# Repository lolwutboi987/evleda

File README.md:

# EvlEDA

EvlEDA is a local KiCad MCP toolbox and PCB-design skill for agents working in chat. Its workspace tools discover approved stock parts, compile design drafts, create and resume native projects, author schematics and PCB geometry, and collect source-bound checks and previews.

Start with the [toolbox guide](docs/toolbox.md), [client setup](docs/toolbox-client-setup.md), and [current status](docs/current-status-and-roadmap.md). The [PCB skill](skills/evleda-pcb/SKILL.md) supplies the engineering workflow; it does not itself supply CAD access.

The [RP2350 prototype handoff](designs/rp2350-pico/PROTOTYPE-HANDOFF.md) includes
a complete KiCad ZIP. R3 is the owner-selected deliverable; USB inrush remains
explicitly deferred to hardware validation. This is not a manufacturing release.

The [RP2350 R3 candidate](designs/rp2350-pico/native-r3-trace/README.md)
includes the routed 22 x 60 mm four-layer board, schematic, portable library,
previews, pinout and candidate BOM. All 67 nets connect; configured ERC/DRC
and portable schematic parity are clean. R3 removes a redundant 3V3 trace loop
without moving parts or vias. The new topology checker verifies 64 routed nets;
two crystal-net pad shapes remain unsupported. All 62 placement checks pass.
Native save, normal close and fresh read-only reopening are verified.
Engineering acceptance remains incomplete, including USB startup and other
electrical requirements described with the candidate.

- `pnpm mcp:toolbox` serves the verified research corpus without opening CAD.
- `pnpm mcp:toolbox:workspace` uses an explicitly configured host profile and workspace for in-chat draft, create, close and resume operations. See the [disabled configuration example](examples/toolbox-workspace.config.toml) before configuring a host.
- Native authoring is bounded by the selected contract, installed runtime and advertised capabilities. Current source supports the V1 routed family and V2 two- or four-layer plane family; verification status and unsupported cases remain explicit.

The [WSON regulator example](examples/wson-regulator-toolbox-proof/README.md) includes the actual KiCad project, native previews and a compact qualification record. Its public-tool authoring and read-only reopen preserve all six source files; unresolved plane and engineering requirements remain explicit. Native checks produce review evidence, not a manufacture-ready verdict. Physical validation, firmware and manufacturing release are outside this active toolbox milestone.

## Preserved application and Flux UI

The sections below document the earlier application and its profile-bound workflows. Their topology and iteration limits apply to those workflows; they are not a replacement for the current chat toolbox documentation. This infrastructure remains in the repository and is deferred from the active development path.

For the candidate-only local Flux workspace, see [docs/flux-local.md](docs/flux-local.md).

Fresh Flux runs allow 1–24 authoring iterations, with 12 recommended and used
by default. The cap is bound by each new run's approval and does not guarantee
success; consumed runs cannot gain more attempts through a policy update.
Standalone copied-board limits remain 1–5/default 3. See the
[iteration and resource budget policy](docs/flux-local.md#iteration-budgets-and-approval)
for standalone fresh defaults, message/byte limits, and unchanged timeouts.

EvlEDA's broad product goal is a
local-first agentic hardware-development application: turn requirements into
evidence-bound review candidates. It coordinates architecture, component
selection, KiCad sources and checks, firmware contracts, manufacturing
outputs, and bring-up documentation without treating generated output as proof.

The implementation is intentionally narrower than that goal. EvlEDA v0 can
parameterize and replay the reviewed `EVL-RC-G0-REV-A` topology only within its
7-16.8 V, two-channel, at-most-0.5 A RMS-per-channel envelope. It does not yet
generate arbitrary hardware topology. A wider envelope or structural change
requires a separately reviewed immutable profile and native design.

Autonomous work can reach `candidate` only. A model statement, clean native
ERC/DRC, route closure, generated CAM, or successful firmware build does not make
a design safe, fabricated, certified, qualified, flashable, production-ready, or
released. Qualification and manufacturing release are distinct human
attestations bound to exact immutable identities and real evidence.

## Implemented workflow

```text
React operator console ─┐
REST /v1 API ───────────┼── application commands ── nine-stage workflow
EvlEDA MCP server ──────┘             │                    │
                                      │                    ├─ policy gates
                                      │                    ├─ constrained tools
                                      │                    └─ evidence projection
                            durable records + content-addressed artifacts
                                                    │
                              pinned KiCad MCP sidecar / KiCad 10 CLI
```

REST and MCP expose the same 14 public workflow operations, including
`inspect_engineering_practices`. Human-only authority remains unavailable to the
agent-facing MCP process. KiCad remains authoritative for native project
semantics, ERC/DRC, rendering, and exports; EvlEDA owns orchestration, typed
transformations, traceability, evidence freshness, and lifecycle policy.

The repository also contains isolated Phase-A agent scaffolding and architecture
IR: role contracts, production-host prerequisites, an authenticated provider
boundary, durable frozen replay receipts, mandatory deterministic validators,
and a system-architecture IR/compiler. That subsystem is not wired into the
application factory/service, REST, MCP, or React UI, and production composition
has no default live provider. It is implemented and tested infrastructure, not
an active agent-driven design path.

## Honest reference-design status

The canonical six-layer Rev-A source opens cleanly and has source-bound native
results with zero ERC, DRC, schematic-parity, and route-closure findings. Native
cleanliness and EvlEDA's route-practice policy are separate checks, however.
Rev-A is deliberately retained as an expected-negative BLOCKED_DIAGNOSTIC proof fixture
for the hard `ROUTE_STYLE` and `BACKTRACK` rules. Its plan records
`expected_negative`; until bound analyzer evidence proves compliant regenerated
geometry, engineering-practice inspection must report `BLOCKED_DIAGNOSTIC`, not
`PROVISIONAL_POC`, manufacture-ready, or release status.

The normal production workflow is independently blocked earlier at component
selection because the captured buck source is unavailable and all eight pin/pad
reviews remain pending. A clean native board does not waive either boundary.
See [the current handoff](HANDOFF.md), the
[reference-design details](reference-designs/robotics-controller-v0/README.md),
and the [PCB engineering-practice contract](docs/pcb-engineering-practices.md).

## Reproducibility and durable-state boundaries

Current exports use `evleda.bundle-manifest.v3`,
`evleda.bundle-export-replay.v2`, and the `deterministic-zip-v3` tool profile.
The manifest, result, and every bundle-generated artifact bind the canonical
`evleda.live-regeneration-policy.v1` identity as an exact input. Live model or
research regeneration is labeled traceable and non-reproducible.

Original unlabeled `evleda.bundle-manifest.v2` manifests and their
`evleda.bundle-export-replay.v1` envelopes remain exact legacy data: they keep
the `deterministic-zip-v2` two-input contract and are never relabeled or given a
synthesized policy. The standalone verifier rejects them by default; explicit
`--allow-legacy-v2` verification recomputes provenance roots but returns the
downgraded `provenance_roots_without_live_policy` assurance. Legacy
`evleda.bundle-manifest.v1` remains a separate explicit byte-integrity-only mode.

Acceptance row W-03 is software-complete: fault injection covers every content
commit boundary and proves partial stage artifacts/evidence never become current.
One P2 lock-hardening `it.todo` test remains for recycled live-PID and
process-incarnation handling; it does not reopen the atomic-publication result.
W-08 is unverified: native KiCad and firmware report artifacts embed invocation
details and identities, but no production application writer populates the
state schema's reserved `ToolInvocationRecord` map. Embedded report evidence is
not a durable first-class invocation ledger.

## Physical and firmware boundaries

The software implements strict `evleda.physical-acceptance.v2`,
`evleda.physical-measurements.v2`, and `evleda.human-physical-evidence.v3`
contracts and exercises their qualification/release gates with test fixtures.
The canonical Rev-A repository has no real built-board acceptance record,
hardware qualification, or manufacturing release. Software fixtures cannot
supply those facts.

The real STM32G0 cross-build snapshots the pinned Arm GNU toolchain and CMSIS
support closure, executes from a verified private workspace with bounded inputs,
and emits identity-bound ELF/BIN/map outputs. Those outputs remain
`compiled-non-flashable-candidate`, with `flashable: false` and no release
authority.

## Development

Requires Node.js 24.19 or newer, pnpm, and KiCad 10.x for native integration.
The optional real KiCad-MCP smoke setup is documented in
[the sidecar verification guide](docs/kicad-mcp-sidecar.md); the identity-bound
STM32G0 cross-build is documented in
[the firmware toolchain guide](docs/firmware-toolchain.md). The 1,773-rule,
17-dossier engineering corpus is a manifest-bound application resource; its
module-relative loading, identity, packaging, and update procedure are in the
[deep-rule resource guide](docs/deep-rule-resources.md).

```powershell
pnpm install --frozen-lockfile
pnpm verify
pnpm dev
```

Runtime state defaults to a local application-data directory and should not live
in the synced source tree. See [the product contract](docs/product-contract.md)
for normative safety and evidence boundaries.

## Verified matrix (2026-09-05)

The latest local verification used Node 24.19.0 and the explicit pinned tool
paths described in `HANDOFF.md`. Targeted rows overlap and must not be added
together.

- Full `node scripts/check.mjs`: 65/65 test files, 929 passed, 1 skip
  (intentional), 1 todo, and 0 failures.
- UI TypeScript: passed; UI Vitest: 10/10 files and 33/33 tests passed.
- Installed-Chrome Playwright: 5/5 passed.
- Real KiCad/reference suites: 4/4 files and 76/76 tests passed.
- Firmware validation: 32 passed and 1 intentional host-compiler skip because
  `EVLEDA_FIRMWARE_CC` was unset; the real Arm cross-build ran and passed.
- Audited `kicad-mcp`: 5/5 passed.
- Evidence and bundle suites: 3/3 files and 43/43 tests passed; standalone
  bundle adversarial verification: 35/35 passed.
- Production build: passed, 92 modules transformed.

These results do not substitute for GitHub CI, fabrication, bench evidence,
qualification, safety review, or release.

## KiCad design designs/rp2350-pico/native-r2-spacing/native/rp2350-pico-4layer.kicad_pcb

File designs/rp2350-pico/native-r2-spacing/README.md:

# RP2350 R2: corrected crystal-block spacing

This **22 x 60 mm, four-layer review candidate** has 1,098 tracks, 118 vias,
62 electrical components and four mounting bores. All 67 functional nets connect.
Configured native ERC/DRC and portable schematic parity are clean. Native save,
normal close and fresh read-only reopening are verified.

Open [the KiCad project](native/rp2350-pico-4layer.kicad_pro) with KiCad 10.0.3,
its stock libraries and the included native/library directory. The package includes
[top](previews/top.png), [assembly](previews/assembly.png), [schematic](previews/schematic.svg),
[pinout](pinout.md), [candidate BOM](bom-candidates.csv) and [BOM notes](bom-notes.md).
R2 names this delivery package; the retained board silkscreen still reads R1.

## Placement correction

The new reusable checker found a 0.02 mm C12–R7 courtyard gap against the
unchanged 0.10 mm requirement. R7 moves 0.10 mm left and the nearby GND via
moves 0.15 mm down to an existing diagonal endpoint. The redundant 0.15 mm
ground stub is removed. The resulting courtyard gap is **0.12 mm**.
All signal tracks, component rotations, via dimensions and clearance requirements
are preserved. Only R7's placement-region minimum X extends from 9.35 to 9.25 mm.
The [revision record](spacing-revision.json) and original failed baseline are retained.

All **62 placement rows** now pass against actual saved geometry and approved
courtyard sources. This checks the declared region, side, rotation, board-edge
bounds and pair spacing; physical housings, fasteners and assembly tolerances
remain separate. The original R1 remains available as historical evidence.

## Routing and checks

Both full-height GPIO service strips are clear of unrelated copper; 42 exact
own-pad inward leads remain. Header pitch/row spacing stay 2.54/17.78 mm.
The current source audit measures **886 straight/45-degree turns
with zero violations**, retaining 6 generic junction notices
and their pad/via attribution. All 19 declared geometric reference rows and
nominal drilled-copper paths from all 64 physical GND pads to the primary plane
pass. Existing debug-terminal launch conditions and margins remain unchanged.

The original [host60 native assessment](../../../proofs/placement-spacing-20260921/public-report.json)
records **225 pass, 349 unknown, 0 fail; accepted=false**. The newer [host62 assessment](../../../proofs/artifact-checks-20260921/fresh-fill-report.json) on these unchanged native files records **495 pass, 79 unknown, 0 fail; accepted=false** after integrating 270 source/native artifact requirements. Unknowns include
unfinished assessment integration plus electrical and construction requirements;
they are not a count of observed defects. USB attach/startup/inrush, current,
voltage drop, physical copper/thermal widths and interface performance remain
open. The board is not yet an electrically accepted or manufacturing-ready design.

Read-only reopening retains placement results and all 67 connected nets without
recreating the earlier session's fresh-fill authority. Its plane/reference rows
remain unknown as returned. The four portable design files are byte-exact;
only the two library-table URI prefixes change for portability.

The native visual heuristic still reports WARN. Its four reference-overlap
warnings use hidden F.Fab fields; its body/off-board estimates center dimensions
on footprint origins. The [source and preview review](verification/visual-review.json)
retains all 13 findings and the actual header courtyards. Both current previews
were visually inspected. This is not a machine-certified visual or assembly pass.

ERC ignores single_global_label, four_way_junction, simulation_model_issue and
footprint_filter. DRC ignores missing_courtyard, track_not_centered_on_via,
tuning_profile_track_geometries, footprint_filters_mismatch and footprint_type_mismatch.
Complete native reports retain checker settings and exclusions.

## Managed continuation

Continue with project **0474c726-1b0c-492b-b376-9c6a06ee9d72** in the existing qualified workspace.
Both edit and fresh read-only sessions closed normally. Parent **f464e518-2b03-453a-9f9c-a31f7d044d4a**
and the older protected allocation remain preserved. No historical lease or
unsafe marker was removed. Host60 is stored on D:, which must stay mounted.
Firmware, physical testing, board ordering and manufacturing release are outside
this delivered scope.

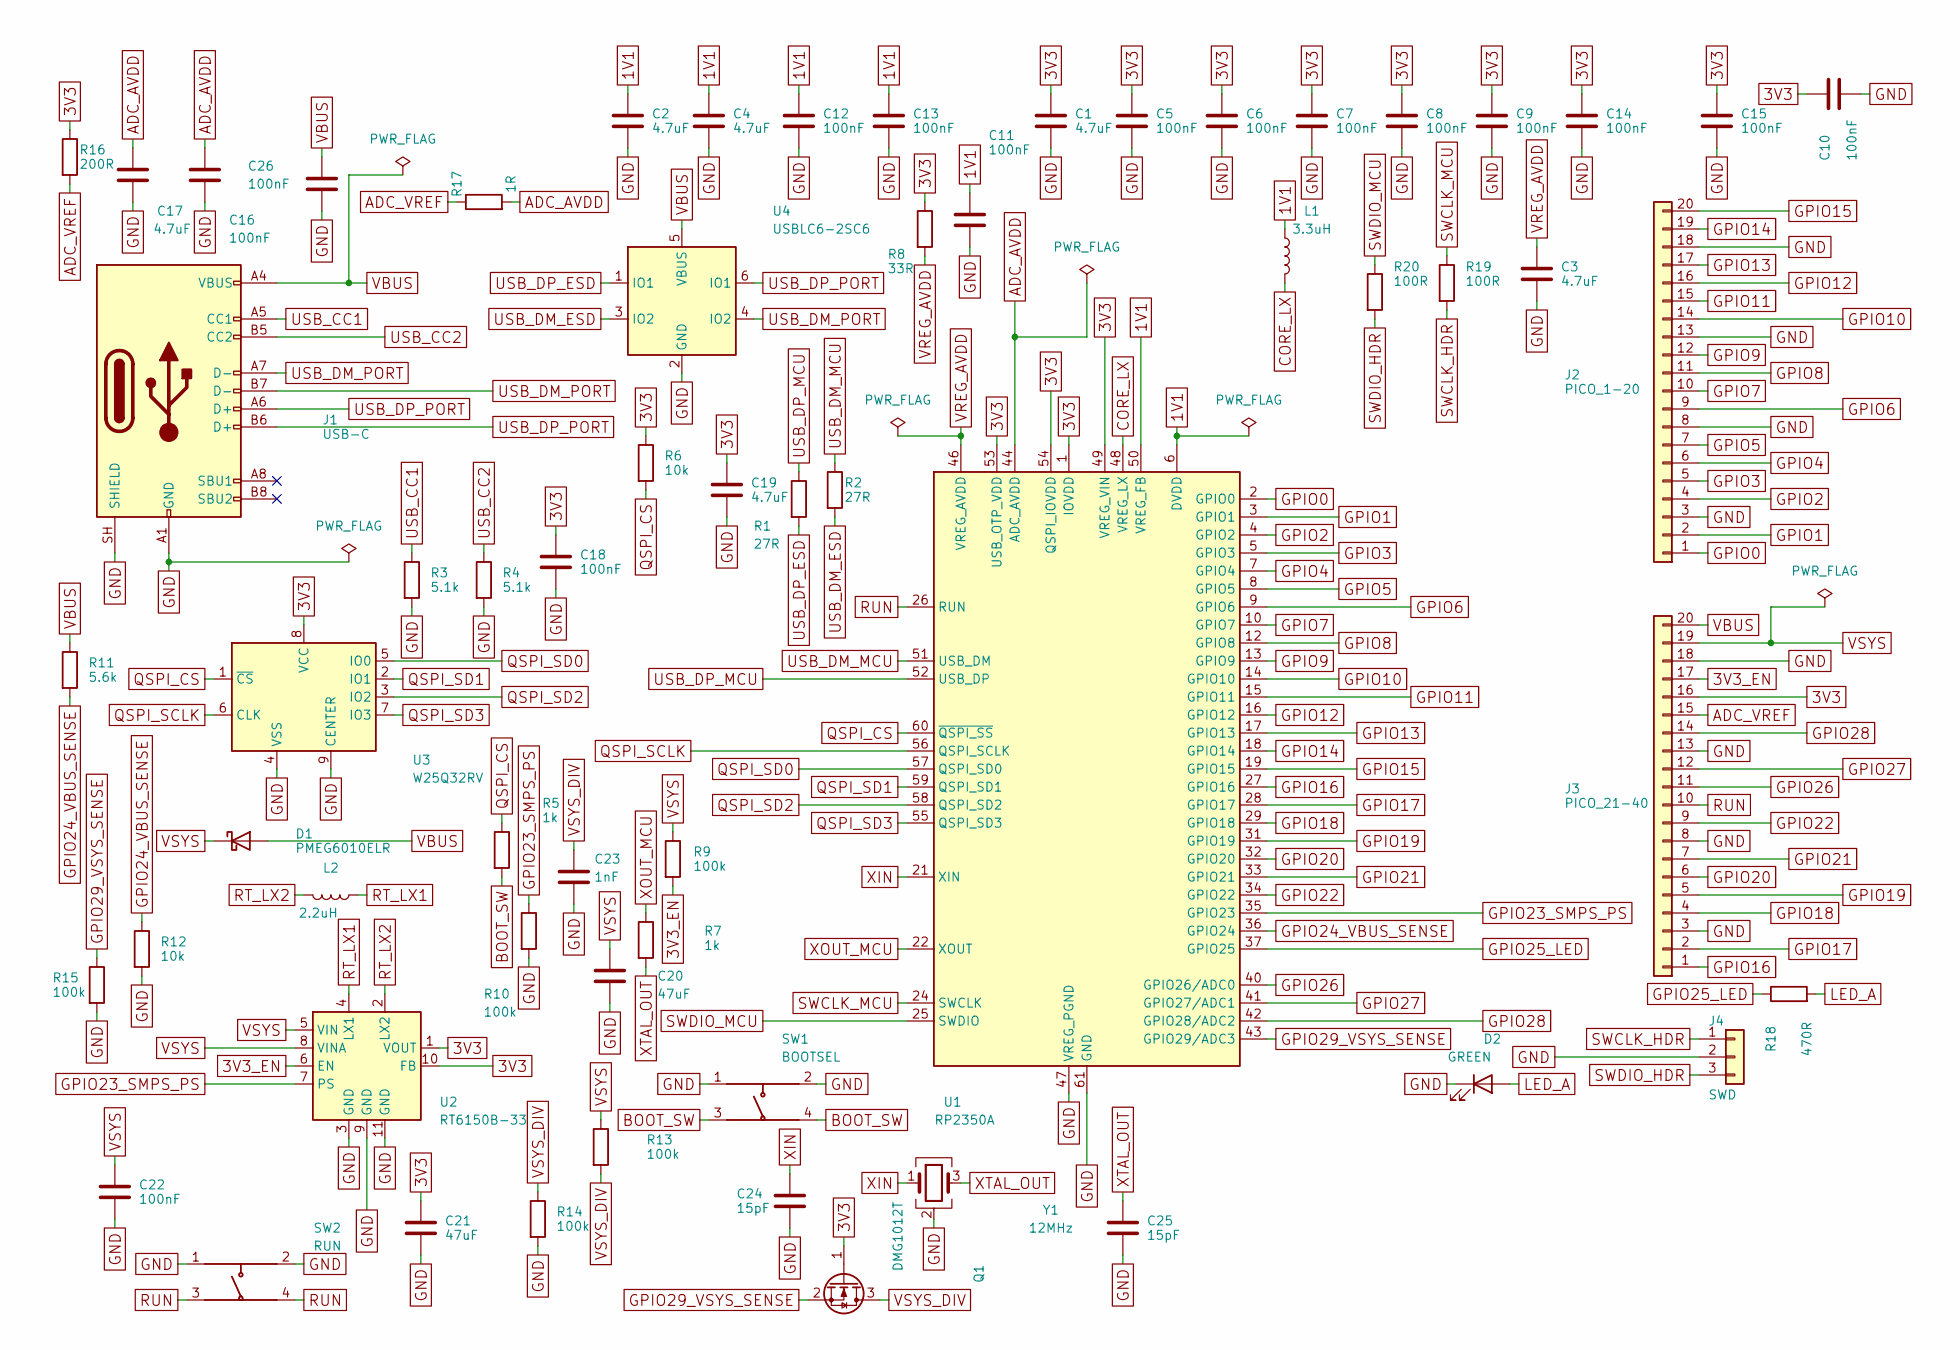
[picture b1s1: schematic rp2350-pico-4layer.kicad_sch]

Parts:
C1, C2, C3, C4, C17, C19: 4.7uF; C_0402_1005Metric
C5, C6, C7, C8, C9, C10, C11, C12, C13, C14, C15, C16, C18, C22, C26: 100nF; C_0402_1005Metric
C20, C21: 47uF; C3225X5R1A476M250AC_TDK_PA2.2_PB1.1_PC2.2
C23: 1nF; C_0402_1005Metric
C24, C25: 15pF; C_0402_1005Metric
D1: PMEG6010ELR; Nexperia_CFP3_SOD-123W
D2: GREEN; LED_0603_1608Metric
J1: USB-C; USB_C_Receptacle_GCT_USB4105-xx-A_16P_TopMnt_Horizontal
J2: PICO_1-20; Pico_BarePTH_1x20_P2.54mm_D1.0mm_Pad1.7mm
J3: PICO_21-40; Pico_BarePTH_1x20_P2.54mm_D1.0mm_Pad1.7mm
J4: SWD; PinHeader_1x03_P2.54mm_Vertical
L1: 3.3uH; AOTA-B201610S3R3-101-T_RaspberryPi_Minimal
L2: 2.2uH; L_Coilcraft_XxL4020
Q1: DMG1012T; SOT-523
R1, R2: 27R; R_0402_1005Metric
R3, R4: 5.1k; R_0402_1005Metric
R5, R7: 1k; R_0402_1005Metric
R6, R12: 10k; R_0402_1005Metric
R8: 33R; R_0402_1005Metric
R9, R10, R13, R14, R15: 100k; R_0402_1005Metric
R11: 5.6k; R_0402_1005Metric
R16: 200R; R_0402_1005Metric
R17: 1R; R_0402_1005Metric
R18: 470R; R_0402_1005Metric
R19, R20: 100R; R_0402_1005Metric
SW1: BOOTSEL; Wuerth_434133025816_4Terminal
SW2: RUN; Wuerth_434133025816_4Terminal
U1: RP2350A; QFN-60-1EP_7x7mm_P0.4mm_EP3.4x3.4mm
U2: RT6150B-33; RT6150B_WDFN-10-1EP_2.5x2.5mm_P0.5mm
U3: W25Q32RV; W25Q32RVXH_XSON-8-1EP_3x2mm_P0.5mm_EP0.2x1.6mm
U4: USBLC6-2SC6; SOT-23-6
Y1: 12MHz; Crystal_SMD_3225-4Pin_3.2x2.5mm

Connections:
1V1: C2.1, C4.1, C11.1, C12.1, C13.1, L1.1, U1.6 (DVDD), U1.23 (DVDD), U1.39 (DVDD), U1.50 (VREG_FB)
3V3: C1.1, C5.1, C6.1, C7.1, C8.1, C9.1, C10.1, C14.1, C15.1, C18.1, C19.1, C21.1, J3.16, Q1.1 (G), R6.1, R8.1, R16.1, U1.1 (IOVDD), U1.11 (IOVDD), U1.20 (IOVDD), U1.30 (IOVDD), U1.38 (IOVDD), U1.45 (IOVDD), U1.49 (VREG_VIN), U1.53 (USB_OTP_VDD), U1.54 (QSPI_IOVDD), U2.1 (VOUT), U2.10 (FB), U3.8 (VCC)
3V3_EN: J3.17, R9.2, U2.6 (EN)
ADC_AVDD: C16.1, C17.1, R17.2, U1.44 (ADC_AVDD)
ADC_VREF: J3.15, R16.2, R17.1
BOOT_SW: R5.2, SW1.3 (B), SW1.4 (B)
CORE_LX: L1.2, U1.48 (VREG_LX)
GND: C1.2, C2.2, C3.2, C4.2, C5.2, C6.2, C7.2, C8.2, C9.2, C10.2, C11.2, C12.2, C13.2, C14.2, C15.2, C16.2, C17.2, C18.2, C19.2, C20.2, C21.2, C22.2, C23.2, C24.2, C25.2, C26.2, D2.1 (K), J1.A1 (GND), J1.A12 (GND), J1.B1 (GND), J1.B12 (GND), J1.SH (SHIELD), J2.3, J2.8, J2.13, J2.18, J3.3, J3.8, J3.13, J3.18, J4.2, R3.2, R4.2, R10.2, R12.2, R14.2, R15.2, SW1.1 (A), SW1.2 (A), SW2.1 (A), SW2.2 (A), U1.47 (VREG_PGND), U1.61 (GND), U2.3 (GND), U2.9 (GND), U2.11 (GND), U3.4 (VSS), U3.9 (CENTER), U4.2 (GND), Y1.2 (G), Y1.4 (G)
GPIO0: J2.1, U1.2 (GPIO0)
GPIO1: J2.2, U1.3 (GPIO1)
GPIO2: J2.4, U1.4 (GPIO2)
GPIO3: J2.5, U1.5 (GPIO3)
GPIO4: J2.6, U1.7 (GPIO4)
GPIO5: J2.7, U1.8 (GPIO5)
GPIO6: J2.9, U1.9 (GPIO6)
GPIO7: J2.10, U1.10 (GPIO7)
GPIO8: J2.11, U1.12 (GPIO8)
GPIO9: J2.12, U1.13 (GPIO9)
GPIO10: J2.14, U1.14 (GPIO10)
GPIO11: J2.15, U1.15 (GPIO11)
GPIO12: J2.16, U1.16 (GPIO12)
GPIO13: J2.17, U1.17 (GPIO13)
GPIO14: J2.19, U1.18 (GPIO14)
GPIO15: J2.20, U1.19 (GPIO15)
GPIO16: J3.1, U1.27 (GPIO16)
GPIO17: J3.2, U1.28 (GPIO17)
GPIO18: J3.4, U1.29 (GPIO18)
GPIO19: J3.5, U1.31 (GPIO19)
GPIO20: J3.6, U1.32 (GPIO20)
GPIO21: J3.7, U1.33 (GPIO21)
GPIO22: J3.9, U1.34 (GPIO22)
GPIO23_SMPS_PS: R10.1, U1.35 (GPIO23), U2.7 (PS)
GPIO24_VBUS_SENSE: R11.2, R12.1, U1.36 (GPIO24)
GPIO25_LED: R18.1, U1.37 (GPIO25)
GPIO26: J3.11, U1.40 (GPIO26/ADC0)
GPIO27: J3.12, U1.41 (GPIO27/ADC1)
GPIO28: J3.14, U1.42 (GPIO28/ADC2)
GPIO29_VSYS_SENSE: Q1.2 (S), R15.1, U1.43 (GPIO29/ADC3)
LED_A: D2.2 (A), R18.2
QSPI_CS: R5.1, R6.2, U1.60 (~QSPI_SS), U3.1 (~CS)
QSPI_SCLK: U1.56 (QSPI_SCLK), U3.6 (CLK)
QSPI_SD0: U1.57 (QSPI_SD0), U3.5 (IO0)
QSPI_SD1: U1.59 (QSPI_SD1), U3.2 (IO1)
QSPI_SD2: U1.58 (QSPI_SD2), U3.3 (IO2)
QSPI_SD3: U1.55 (QSPI_SD3), U3.7 (IO3)
RT_LX1: L2.1, U2.4 (LX1)
RT_LX2: L2.2, U2.2 (LX2)
RUN: J3.10, SW2.3 (B), SW2.4 (B), U1.26 (RUN)
SWCLK_HDR: J4.1, R19.2
SWCLK_MCU: R19.1, U1.24 (SWCLK)
SWDIO_HDR: J4.3, R20.2
SWDIO_MCU: R20.1, U1.25 (SWDIO)
USB_CC1: J1.A5 (CC1), R3.1
USB_CC2: J1.B5 (CC2), R4.1
USB_DM_ESD: R2.2, U4.3 (IO2)
USB_DM_MCU: R2.1, U1.51 (USB_DM)
USB_DM_PORT: J1.A7 (D-), J1.B7 (D-), U4.4 (IO2)
USB_DP_ESD: R1.2, U4.1 (IO1)
USB_DP_MCU: R1.1, U1.52 (USB_DP)
USB_DP_PORT: J1.A6 (D+), J1.B6 (D+), U4.6 (IO1)
VBUS: C26.1, D1.2 (A), J1.A4 (VBUS), J1.A9 (VBUS), J1.B4 (VBUS), J1.B9 (VBUS), J3.20, R11.1, U4.5 (VBUS)
VREG_AVDD: C3.1, R8.2, U1.46 (VREG_AVDD)
VSYS: C20.1, C22.1, D1.1 (K), J3.19, R9.1, R13.1, U2.5 (VIN), U2.8 (VINA)
VSYS_DIV: C23.1, Q1.3 (D), R13.2, R14.1
XIN: C24.1, U1.21 (XIN), Y1.1
XOUT_MCU: R7.1, U1.22 (XOUT)
XTAL_OUT: C25.1, R7.2, Y1.3

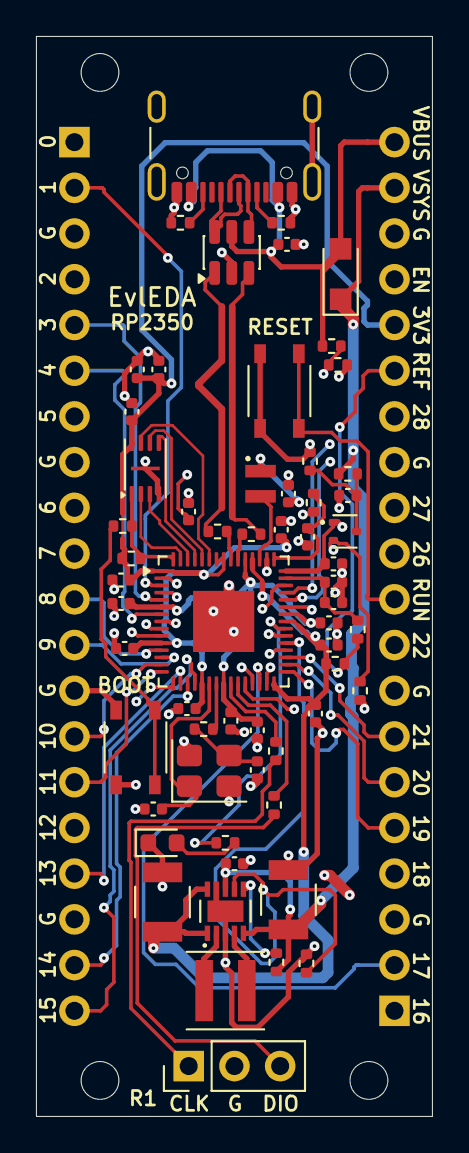
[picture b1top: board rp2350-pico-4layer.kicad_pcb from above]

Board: 4 copper layers, 22.0 x 60.0 mm, 66 parts (0 on the bottom side), 67 nets.

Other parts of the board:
H1, H2, H3, H4: 2.1 mm bare NPTH mounting bore; MountingHole_D2.1_Pico

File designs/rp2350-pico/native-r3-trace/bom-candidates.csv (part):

"reference","quantity","value","mpn","footprint","selectionBasis","sourceIds","notes"
"C1","1","4.7uF","GRM155R60J475ME47D","Capacitor_SMD:C_0402_1005Metric","component-selection.json","K;M47;D;P","Candidate part; retain source conditions and derating"
"C2","1","4.7uF","GRM155R60J475ME47D","Capacitor_SMD:C_0402_1005Metric","component-selection.json","K;M47;D;P","Candidate part; retain source conditions and derating"
"C3","1","4.7uF","GRM155R60J475ME47D","Capacitor_SMD:C_0402_1005Metric","component-selection.json","K;M47;D;P","Candidate part; retain source conditions and derating"
"C4","1","4.7uF","GRM155R60J475ME47D","Capacitor_SMD:C_0402_1005Metric","component-selection.json","K;M47;D;P","Candidate part; retain source conditions and derating"
"C5","1","100nF","GRM155R71E104KE14D","Capacitor_SMD:C_0402_1005Metric","component-selection.json","K;M100","Candidate part; retain source conditions and derating"
"C6","1","100nF","GRM155R71E104KE14D","Capacitor_SMD:C_0402_1005Metric","component-selection.json","K;M100","Candidate part; retain source conditions and derating"
"C7","1","100nF","GRM155R71E104KE14D","Capacitor_SMD:C_0402_1005Metric","component-selection.json","K;M100","Candidate part; retain source conditions and derating"
"C8","1","100nF","GRM155R71E104KE14D","Capacitor_SMD:C_0402_1005Metric","component-selection.json","K;M100","Candidate part; retain source conditions and derating"
"C9","1","100nF","GRM155R71E104KE14D","Capacitor_SMD:C_0402_1005Metric","component-selection.json","K;M100","Candidate part; retain source conditions and derating"
"C10","1","100nF","GRM155R71E104KE14D","Capacitor_SMD:C_0402_1005Metric","component-selection.json","K;M100","Candidate part; retain source conditions and derating"
"C11","1","100nF","GRM155R71E104KE14D","Capacitor_SMD:C_0402_1005Metric","component-selection.json","K;M100","Candidate part; retain source conditions and derating"
"C12","1","100nF","GRM155R71E104KE14D","Capacitor_SMD:C_0402_1005Metric","component-selection.json","K;M100","Candidate part; retain source conditions and derating"
"C13","1","100nF","GRM155R71E104KE14D","Capacitor_SMD:C_0402_1005Metric","component-selection.json","K;M100","Candidate part; retain source conditions and derating"
"C14","1","100nF","GRM155R71E104KE14D","Capacitor_SMD:C_0402_1005Metric","component-selection.json","K;M100","Candidate part; retain source conditions and derating"
"C15","1","100nF","GRM155R71E104KE14D","Capacitor_SMD:C_0402_1005Metric","component-selection.json","K;M100","Candidate part; retain source conditions and derating"
"C16","1","100nF","GRM155R71E104KE14D","Capacitor_SMD:C_0402_1005Metric","component-selection.json","K;M100","Candidate part; retain source conditions and derating"
"C17","1","4.7uF","GRM155R60J475ME47D","Capacitor_SMD:C_0402_1005Metric","component-selection.json","K;M47;D;P","Candidate part; retain source conditions and derating"
"C18","1","100nF","GRM155R71E104KE14D","Capacitor_SMD:C_0402_1005Metric","component-selection.json","K;M100","Candidate part; retain source conditions and derating"
"C19","1","4.7uF","GRM155R60J475ME47D","Capacitor_SMD:C_0402_1005Metric","component-selection.json","K;M47;D;P","Candidate part; retain source conditions and derating"
"C20","1","47uF","C3225X5R1A476M250AC","EvlEDA_Pico2350:C3225X5R1A476M250AC_TDK_PA2.2_PB1.1_PC2.2","component-selection.json","BULK;BULK_CURVE;R;P","Native custom land differs from the earlier stock candidate; see bundled library provenance"
"C21","1","47uF","C3225X5R1A476M250AC","EvlEDA_Pico2350:C3225X5R1A476M250AC_TDK_PA2.2_PB1.1_PC2.2","component-selection.json","BULK;BULK_CURVE;R;P","Native custom land differs from the earlier stock candidate; see bundled library provenance"
"C22","1","100nF","GRM155R71E104KE14D","Capacitor_SMD:C_0402_1005Metric","component-selection.json","K;M100","Candidate part; retain source conditions and derating"
"C23","1","1nF","C1005X7R1H102K050BA","Capacitor_SMD:C_0402_1005Metric","component-selection.json","T1","Candidate part; retain source conditions and derating"
"C24","1","15pF","GRM1555C1H150JA01D","Capacitor_SMD:C_0402_1005Metric","component-selection.json","K;M15","Candidate part; retain source conditions and derating"
"C25","1","15pF","GRM1555C1H150JA01D","Capacitor_SMD:C_0402_1005Metric","component-selection.json","K;M15","Candidate part; retain source conditions and derating"
"C26","1","100nF","GRM155R71E104KE14D","Capacitor_SMD:C_0402_1005Metric","component-selection.json","K;M100","Candidate part; retain source conditions and derating"
"D1","1","PMEG6010ELR","PMEG6010ELR","Diode_SMD:Nexperia_CFP3_SOD-123W","circuit-inputs.json","N;P","Candidate part; retain source conditions and derating"
"D2","1","GREEN","APT1608CGCK","LED_SMD:LED_0603_1608Metric","component-selection.json","LED","Candidate part; retain source conditions and derating"
"J1","1","USB-C","USB4105-GF-A","Connector_USB:USB_C_Receptacle_GCT_USB4105-xx-A_16P_TopMnt_Horizontal","circuit-inputs.json","G;CC","Candidate part; retain source conditions and derating"
"J2","1","PICO_1-20","","EvlEDA_Pico2350:Pico_BarePTH_1x20_P2.54mm_D1.0mm_Pad1.7mm","circuit-inputs.json","P","Board contacts; fitted header MPN is not selected"
"J3","1","PICO_21-40","","EvlEDA_Pico2350:Pico_BarePTH_1x20_P2.54mm_D1.0mm_Pad1.7mm","circuit-inputs.json","P","Board contacts; fitted header MPN is not selected"
"J4","1","SWD","","Connector_PinHeader_2.54mm:PinHeader_1x03_P2.54mm_Vertical","circuit-inputs.json","P","Board contacts; fitted header MPN is not selected"
"L1","1","3.3uH","AOTA-B201610S3R3-101-T","EvlEDA_Pico2350:AOTA-B201610S3R3-101-T_RaspberryPi_Minimal","component-selection.json","K;A;D","Candidate part; retain source conditions and derating"
"L2","1","2.2uH","XFL4020-222MEC","Inductor_SMD:L_Coilcraft_XxL4020","component-selection.json","COIL;R","Candidate part; retain source conditions and derating"
"Q1","1","DMG1012T","DMG1012T-7","Package_TO_SOT_SMD:SOT-523","circuit-inputs.json","Q;P","Candidate part; retain source conditions and derating"
"R1","1","27R","RC0402FR-0727RL","Resistor_SMD:R_0402_1005Metric","component-selection.json","K;YR1","Candidate part; retain source conditions and derating"
"R2","1","27R","RC0402FR-0727RL","Resistor_SMD:R_0402_1005Metric","component-selection.json","K;YR1","Candidate part; retain source conditions and derating"
"R3","1","5.1k","RC0402FR-075K1L","Resistor_SMD:R_0402_1005Metric","component-selection.json","YR2","Candidate part; retain source conditions and derating"
"R4","1","5.1k","RC0402FR-075K1L","Resistor_SMD:R_0402_1005Metric","component-selection.json","YR2","Candidate part; retain source conditions and derating"
"R5","1","1k","RC0402FR-071KL","Resistor_SMD:R_0402_1005Metric","component-selection.json","K;YR3","Candidate part; retain source conditions and derating"
"R6","1","10k","RC0402FR-0710KL","Resistor_SMD:R_0402_1005Metric","component-selection.json","K;YR4","Candidate part; retain source conditions and derating"
"R7","1","1k","RC0402FR-071KL","Resistor_SMD:R_0402_1005Metric","component-selection.json","K;YR3","Candidate part; retain source conditions and derating"
"R8","1","33R","RC0402FR-0733RL","Resistor_SMD:R_0402_1005Metric","component-selection.json","K;YR5","Candidate part; retain source conditions and derating"
"R9","1","100k","RC0402FR-07100KL","Resistor_SMD:R_0402_1005Metric","component-selection.json","YR6","Candidate part; retain source conditions and derating"
"R10","1","100k","RC0402FR-07100KL","Resistor_SMD:R_0402_1005Metric","component-selection.json","YR6","Candidate part; retain source conditions and derating"
"R11","1","5.6k","RC0402FR-075K6L","Resistor_SMD:R_0402_1005Metric","component-selection.json","YR7","Candidate part; retain source conditions and derating"
"R12","1","10k","RC0402FR-0710KL","Resistor_SMD:R_0402_1005Metric","component-selection.json","K;YR4","Candidate part; retain source conditions and derating"
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
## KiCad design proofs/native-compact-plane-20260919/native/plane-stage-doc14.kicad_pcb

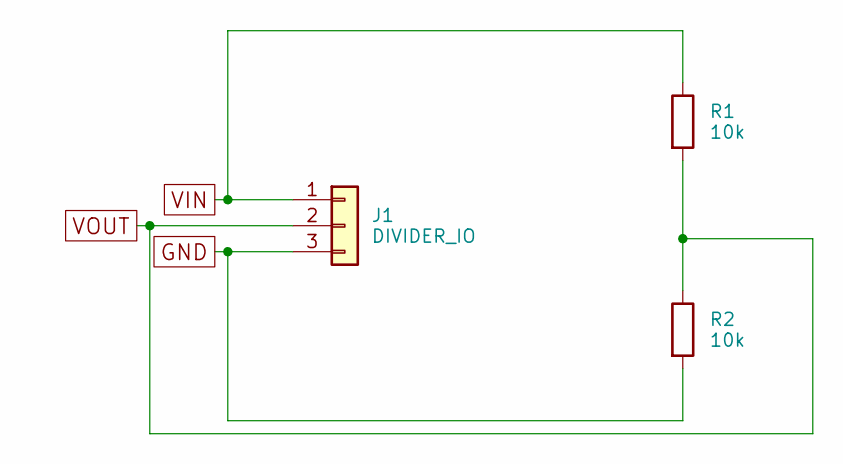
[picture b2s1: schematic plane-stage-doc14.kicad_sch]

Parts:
J1: DIVIDER_IO; PinHeader_1x03_P2.54mm_Vertical
R1, R2: 10k; R_0603_1608Metric

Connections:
GND: J1.3, R2.2
VIN: J1.1, R1.1
VOUT: J1.2, R1.2, R2.1

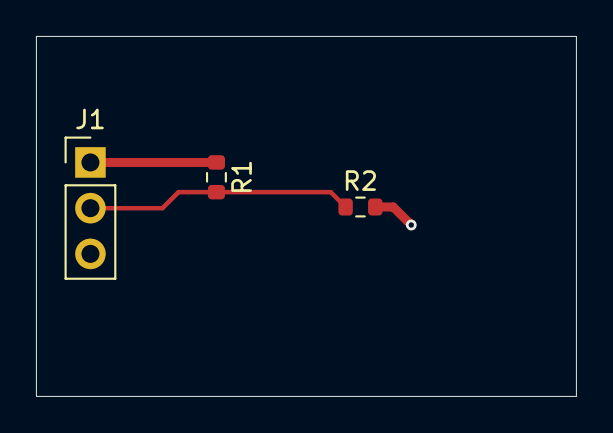
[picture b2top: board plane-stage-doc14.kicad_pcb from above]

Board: 2 copper layers, 30.0 x 20.0 mm, 3 parts (0 on the bottom side), 3 nets.

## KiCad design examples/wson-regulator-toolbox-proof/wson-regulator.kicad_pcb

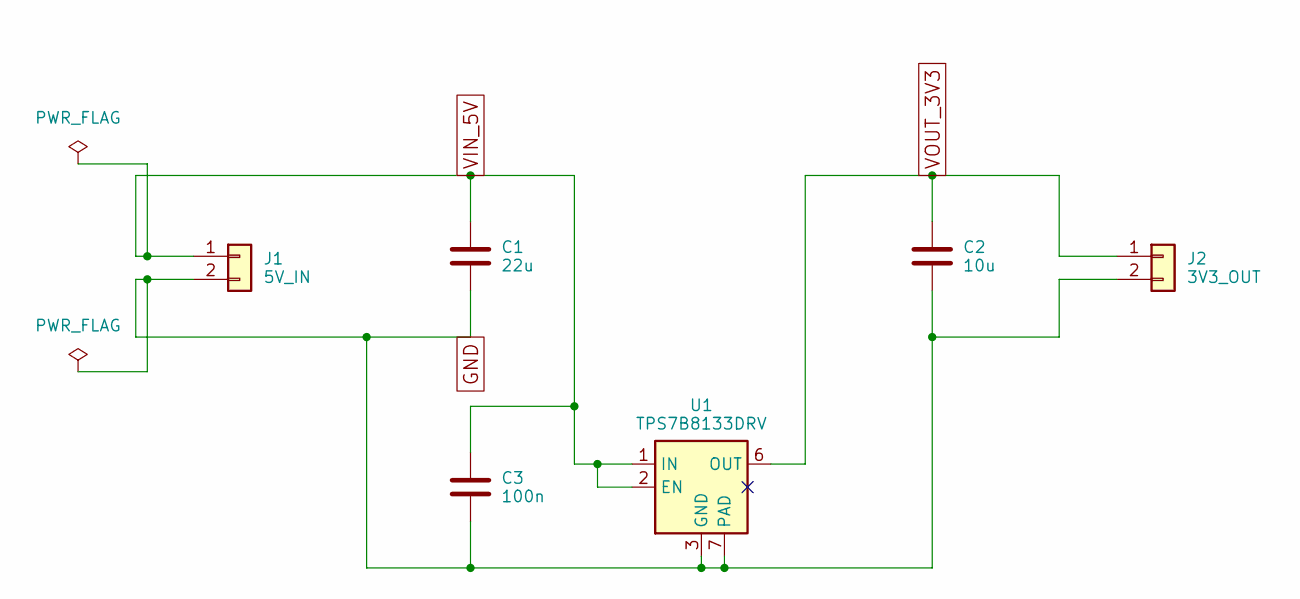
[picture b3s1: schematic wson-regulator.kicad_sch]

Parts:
C1: 22u; C_1210_3225Metric
C2: 10u; C_0805_2012Metric
C3: 100n; C_0402_1005Metric
J1: 5V_IN; PinHeader_1x02_P2.54mm_Vertical
J2: 3V3_OUT; PinHeader_1x02_P2.54mm_Vertical
U1: TPS7B8133DRV; WSON-6-1EP_2x2mm_P0.65mm_EP1x1.6mm

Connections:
GND: C1.2, C2.2, C3.2, J1.2, J2.2, U1.3 (GND), U1.4 (GND), U1.7 (PAD)
VIN_5V: C1.1, C3.1, J1.1, U1.1 (IN), U1.2 (EN)
VOUT_3V3: C2.1, J2.1, U1.6 (OUT)

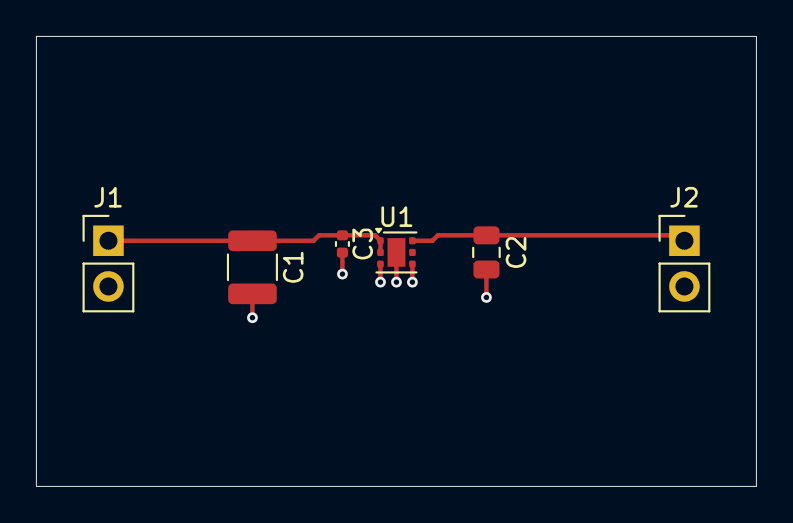
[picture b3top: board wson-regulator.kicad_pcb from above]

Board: 2 copper layers, 40.0 x 25.0 mm, 6 parts (0 on the bottom side), 3 nets.

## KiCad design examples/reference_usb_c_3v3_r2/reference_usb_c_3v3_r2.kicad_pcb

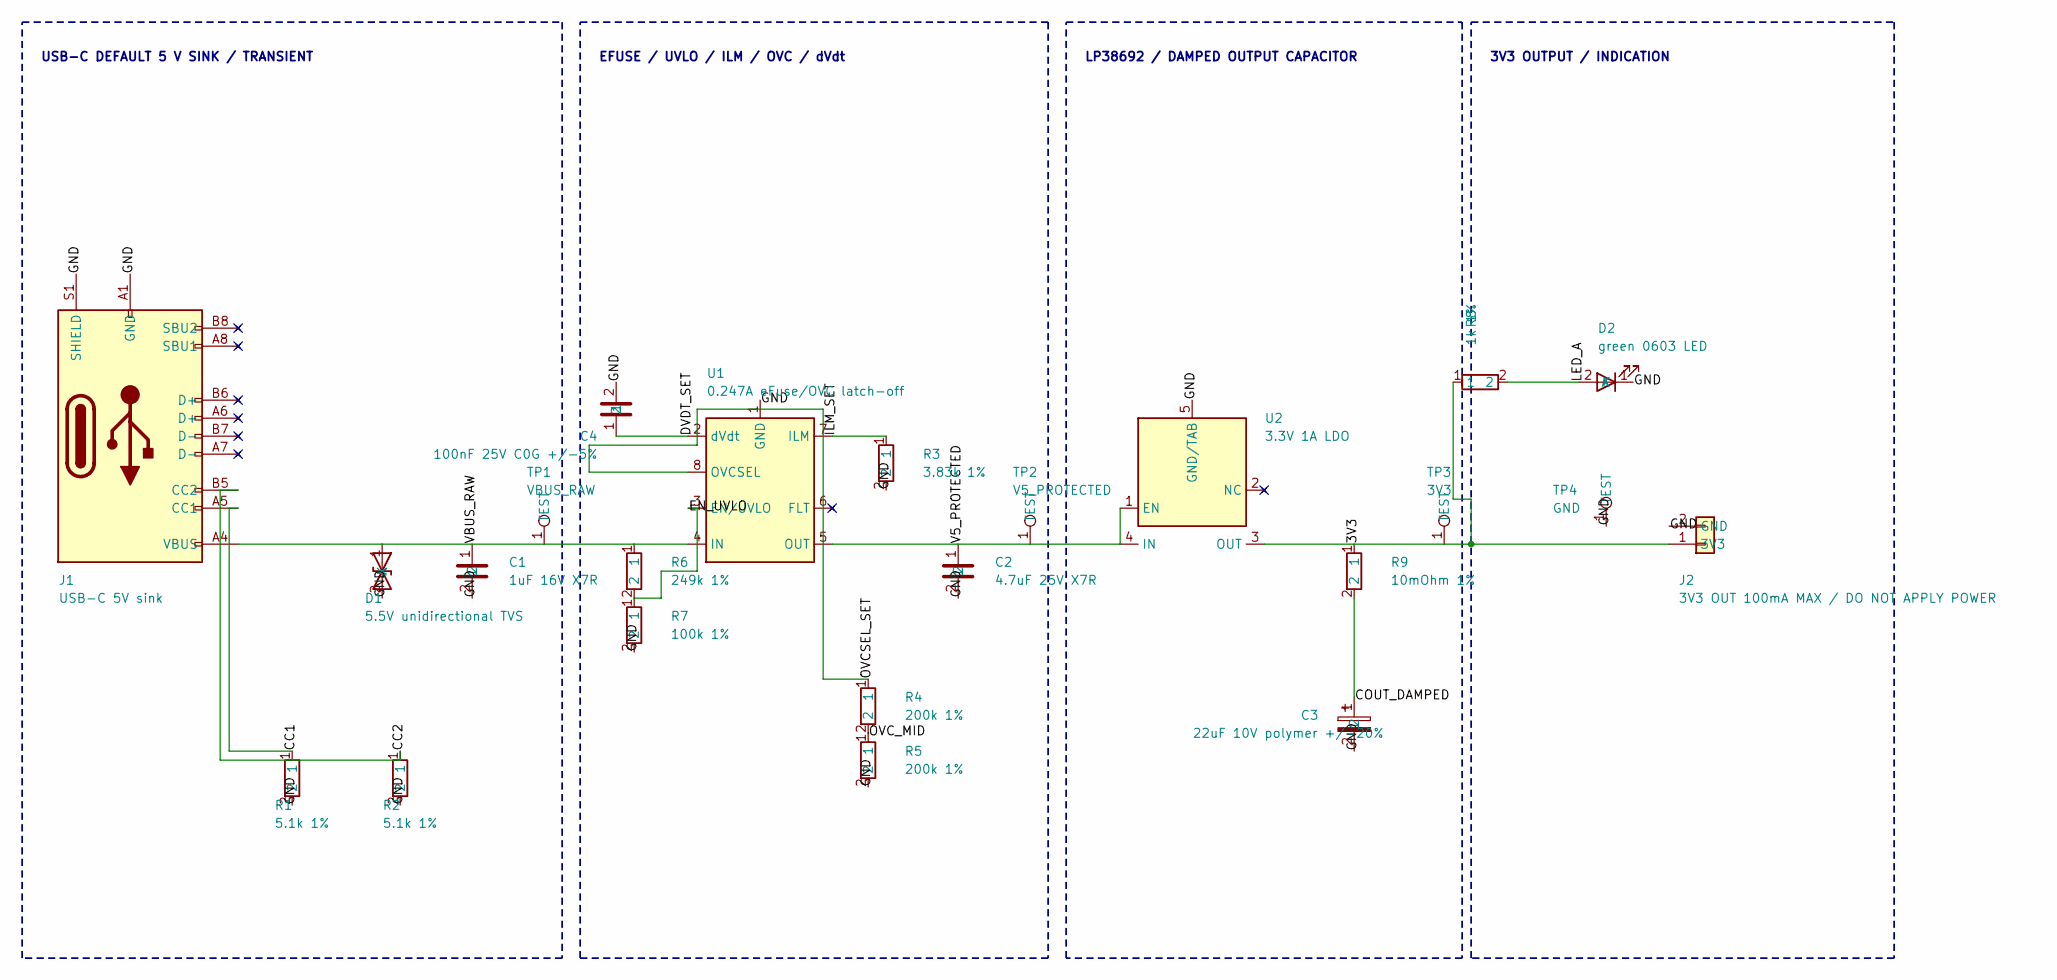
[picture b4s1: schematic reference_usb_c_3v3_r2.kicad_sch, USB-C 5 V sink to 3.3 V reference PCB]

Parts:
C1: 1uF 16V X7R; fp_28444cc44b245b32932e3c565fab864f; ManufacturerPartNumber 885012207051
C2: 4.7uF 25V X7R; fp_94882bf011bc5f1e87e4d85eee6343ee; ManufacturerPartNumber C0805C475K3RACTU
C3: 22uF 10V polymer +/-20%; fp_8e8257a25c905439acc2c3b5f98b1773; ManufacturerPartNumber T598B226M010ATE070
C4: 100nF 25V C0G +/-5%; fp_f05ca65025de54698aa04f889cf47686; ManufacturerPartNumber C1206C104J3GACTU
D1: 5.5V unidirectional TVS; fp_929f98521d3156dda8c73d91d0622a82; ManufacturerPartNumber PTVS5V5Z1UPC
D2: green 0603 LED; fp_2e6b5cac73ae53399429af7b381e190a; ManufacturerPartNumber 150060VS75000
J1: USB-C 5V sink; fp_b854396d140d58c6a824a7f89b75ad9e; ManufacturerPartNumber USB4105-GF-A
J2: 3V3 OUT 100mA MAX / DO NOT APPLY POWER; fp_c3c523f49a555f1b812006a8faf7f241; ManufacturerPartNumber 61300211121
R1: 5.1k 1%; fp_c36a820555e9516cab46827f347b914e; ManufacturerPartNumber CRCW06035K10FKEA
R2: 5.1k 1%; fp_61ca670da6f25095bf4bb2528b3dc8c6; ManufacturerPartNumber CRCW06035K10FKEA
R3: 3.83k 1%; fp_f4348b9e701754f5a067cdbaf9dc46a6; ManufacturerPartNumber CRCW06033K83FKEA
R4: 200k 1%; fp_d6f66386fa4d59b88b037b6158b253de; ManufacturerPartNumber CRCW0603200KFKEA
R5: 200k 1%; fp_3163cbb05ab85a1f898c4cf9d50a1faf; ManufacturerPartNumber CRCW0603200KFKEA
R6: 249k 1%; fp_0103de7ad7895269a7c4e91d7b1dbdc5; ManufacturerPartNumber CRCW0603249KFKEA
R7: 100k 1%; fp_d99751e93f3256fd8c87b489a89e8300; ManufacturerPartNumber CRCW0603100KFKEA
R8: 1k 1%; fp_9d00c8daf3f55af19c700b7644697803; ManufacturerPartNumber CRCW06031K00FKEA
R9: 10mOhm 1%; fp_a78d751717985e30a9b25a0cb605c4c8; ManufacturerPartNumber WSLP0603R0100FEA
TP1: VBUS_RAW; fp_27ac22f87e2a5f909718f99a7580d7b8; ManufacturerPartNumber 5015
TP2: V5_PROTECTED; fp_9594eee5612e51d184b21d9037a20fdb; ManufacturerPartNumber 5015
TP3: 3V3; fp_9742af839cae5d1ca864cdcc649a4639; ManufacturerPartNumber 5015
TP4: GND; fp_f6ef917635c75d7ead58f80bfe8f17b8; ManufacturerPartNumber 5015
U1: 0.247A eFuse/OVC latch-off; fp_5564ef8e90135a4cab1a74819024c718; ManufacturerPartNumber TPS259620DDAR
U2: 3.3V 1A LDO; fp_7794963ceebb5e36b7b6c301eeb69b9b; ManufacturerPartNumber LP38692MPX-3.3/NOPB

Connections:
/3V3: J2.1 (3V3), R8.1, R9.1, TP3.1 (TEST), U2.3 (OUT)
/CC1: J1.A5 (CC1), R1.1
/CC2: J1.B5 (CC2), R2.1
/COUT_DAMPED: C3.1, R9.2
/DVDT_SET: C4.1, U1.2 (dVdt)
/EN_UVLO: R6.2, R7.1, U1.3 (EN/UVLO)
/GND: C1.2, C2.2, C3.2, C4.2, D1.2 (A), D2.1 (K), J1.A1 (GND), J1.A12 (GND), J1.B1 (GND), J1.B12 (GND), J1.S1 (SHIELD), J2.2 (GND), R1.2, R2.2, R3.2, R5.2, R7.2, TP4.1 (TEST), U1.1 (GND), U1.9 (EXPOSED_PAD), U2.5 (GND/TAB)
/ILM_SET: R3.1, U1.7 (ILM)
/LED_A: D2.2 (A), R8.2
/OVCSEL_SET: R4.1, U1.8 (OVCSEL)
/OVC_MID: R4.2, R5.1
/V5_PROTECTED: C2.1, TP2.1 (TEST), U1.5 (OUT), U2.1 (EN), U2.4 (IN)
/VBUS_RAW: C1.1, D1.1 (K), J1.A4 (VBUS), J1.A9 (VBUS), J1.B4 (VBUS), J1.B9 (VBUS), R6.1, TP1.1 (TEST), U1.4 (IN)

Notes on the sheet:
3V3 OUTPUT / INDICATION
EFUSE / UVLO / ILM / OVC / dVdt
LP38692 / DAMPED OUTPUT CAPACITOR
USB-C DEFAULT 5 V SINK / TRANSIENT

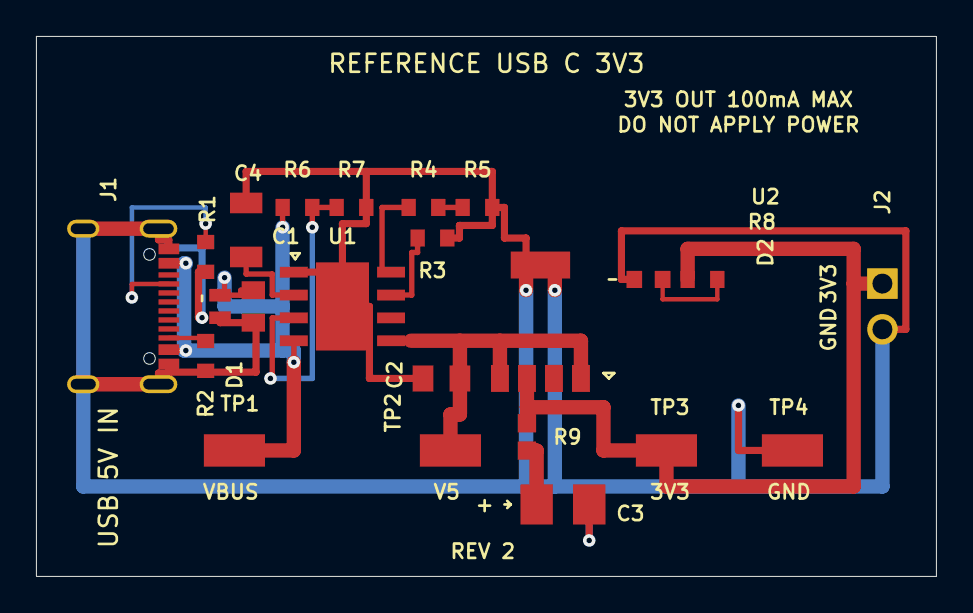
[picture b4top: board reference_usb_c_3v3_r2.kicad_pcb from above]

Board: 2 copper layers, 50.0 x 30.0 mm, 23 parts (0 on the bottom side), 13 nets.
